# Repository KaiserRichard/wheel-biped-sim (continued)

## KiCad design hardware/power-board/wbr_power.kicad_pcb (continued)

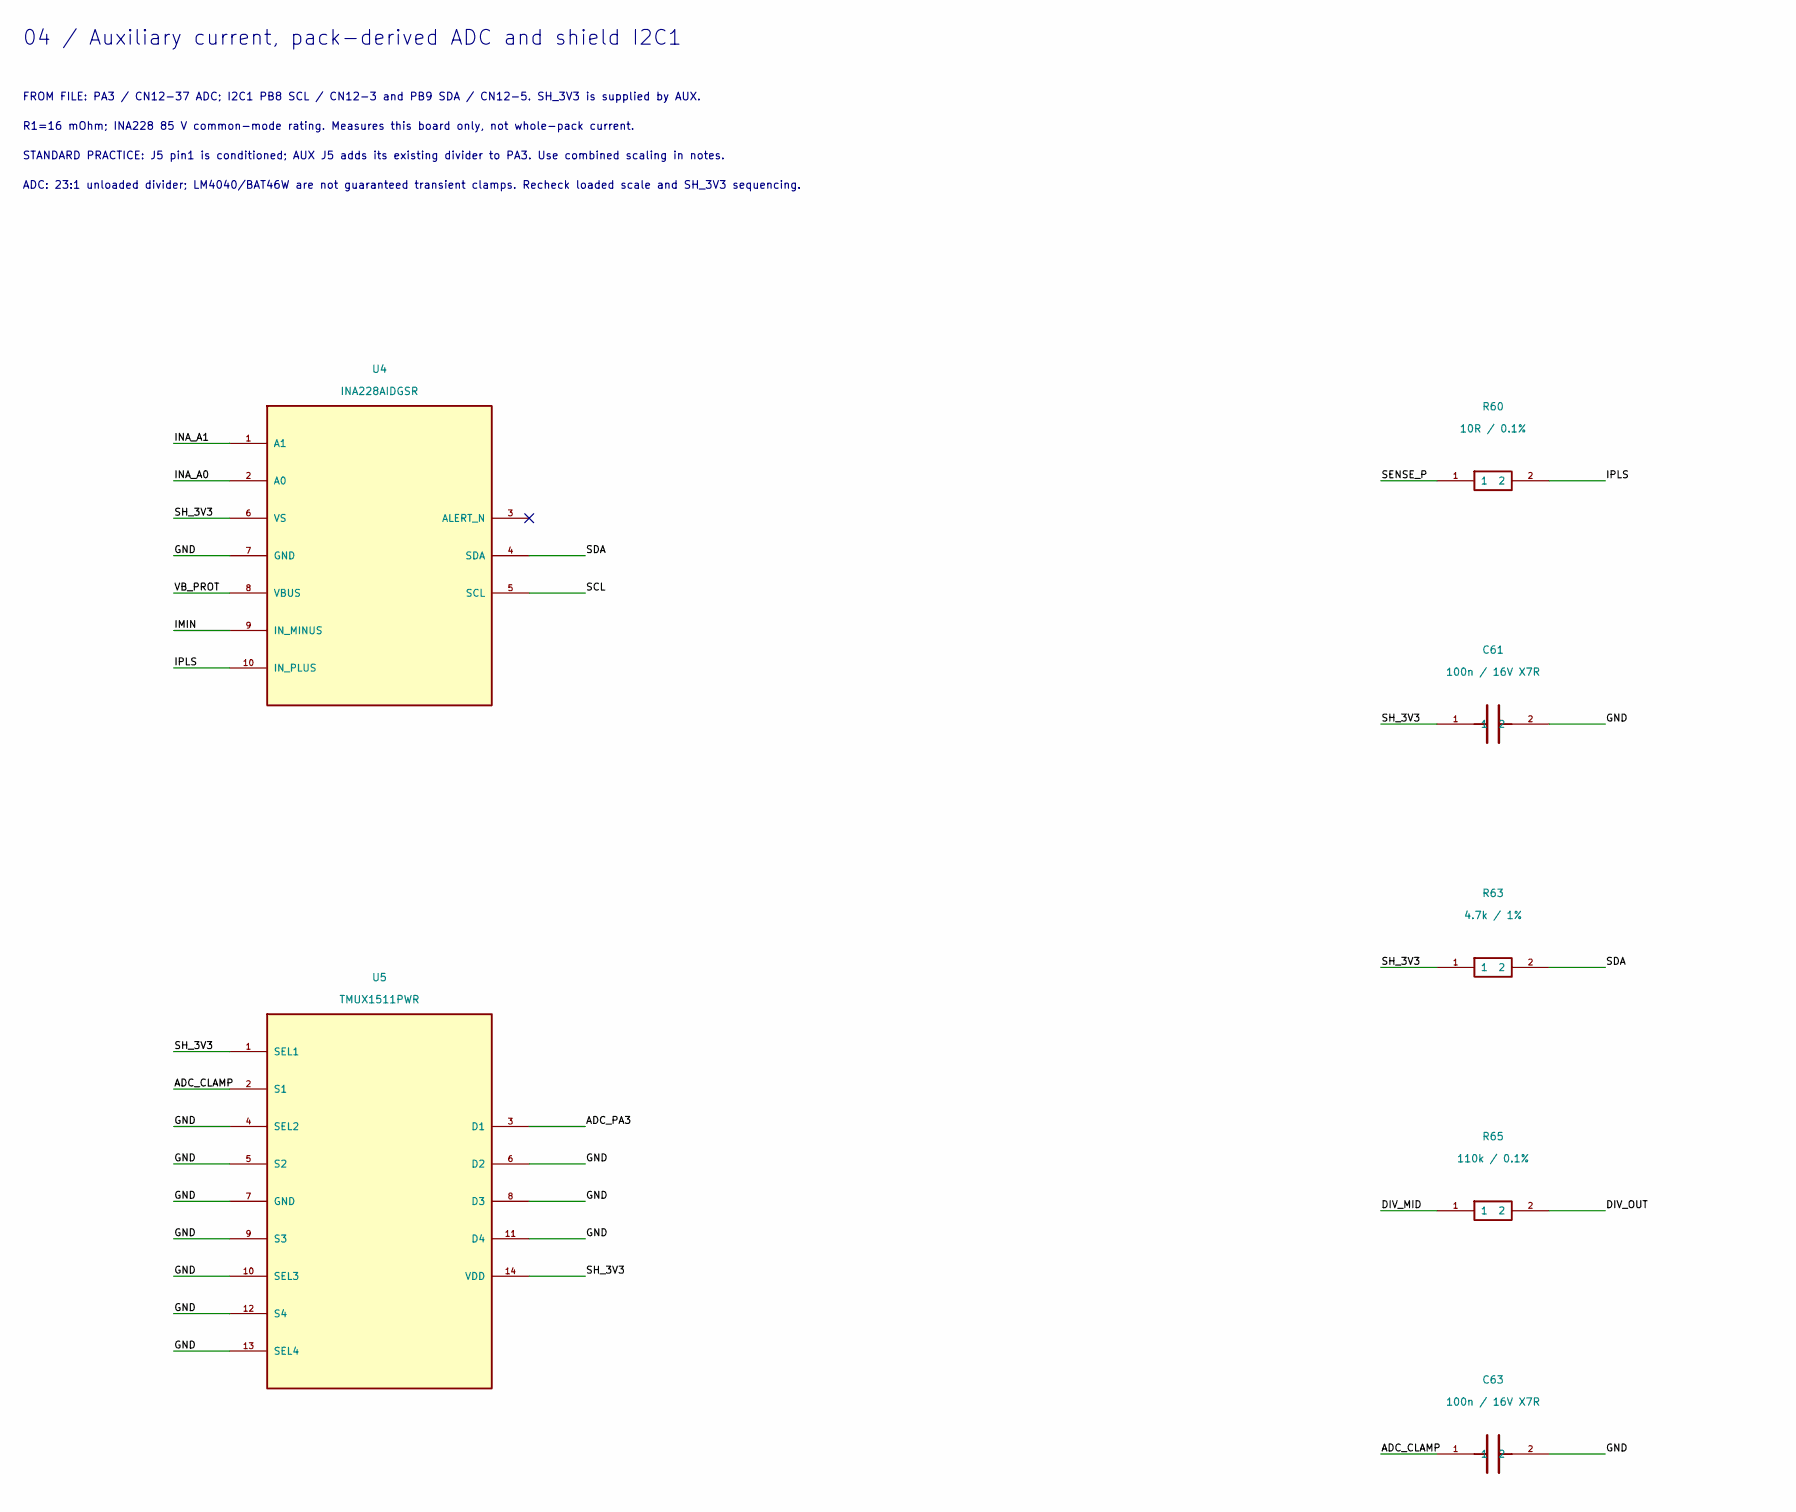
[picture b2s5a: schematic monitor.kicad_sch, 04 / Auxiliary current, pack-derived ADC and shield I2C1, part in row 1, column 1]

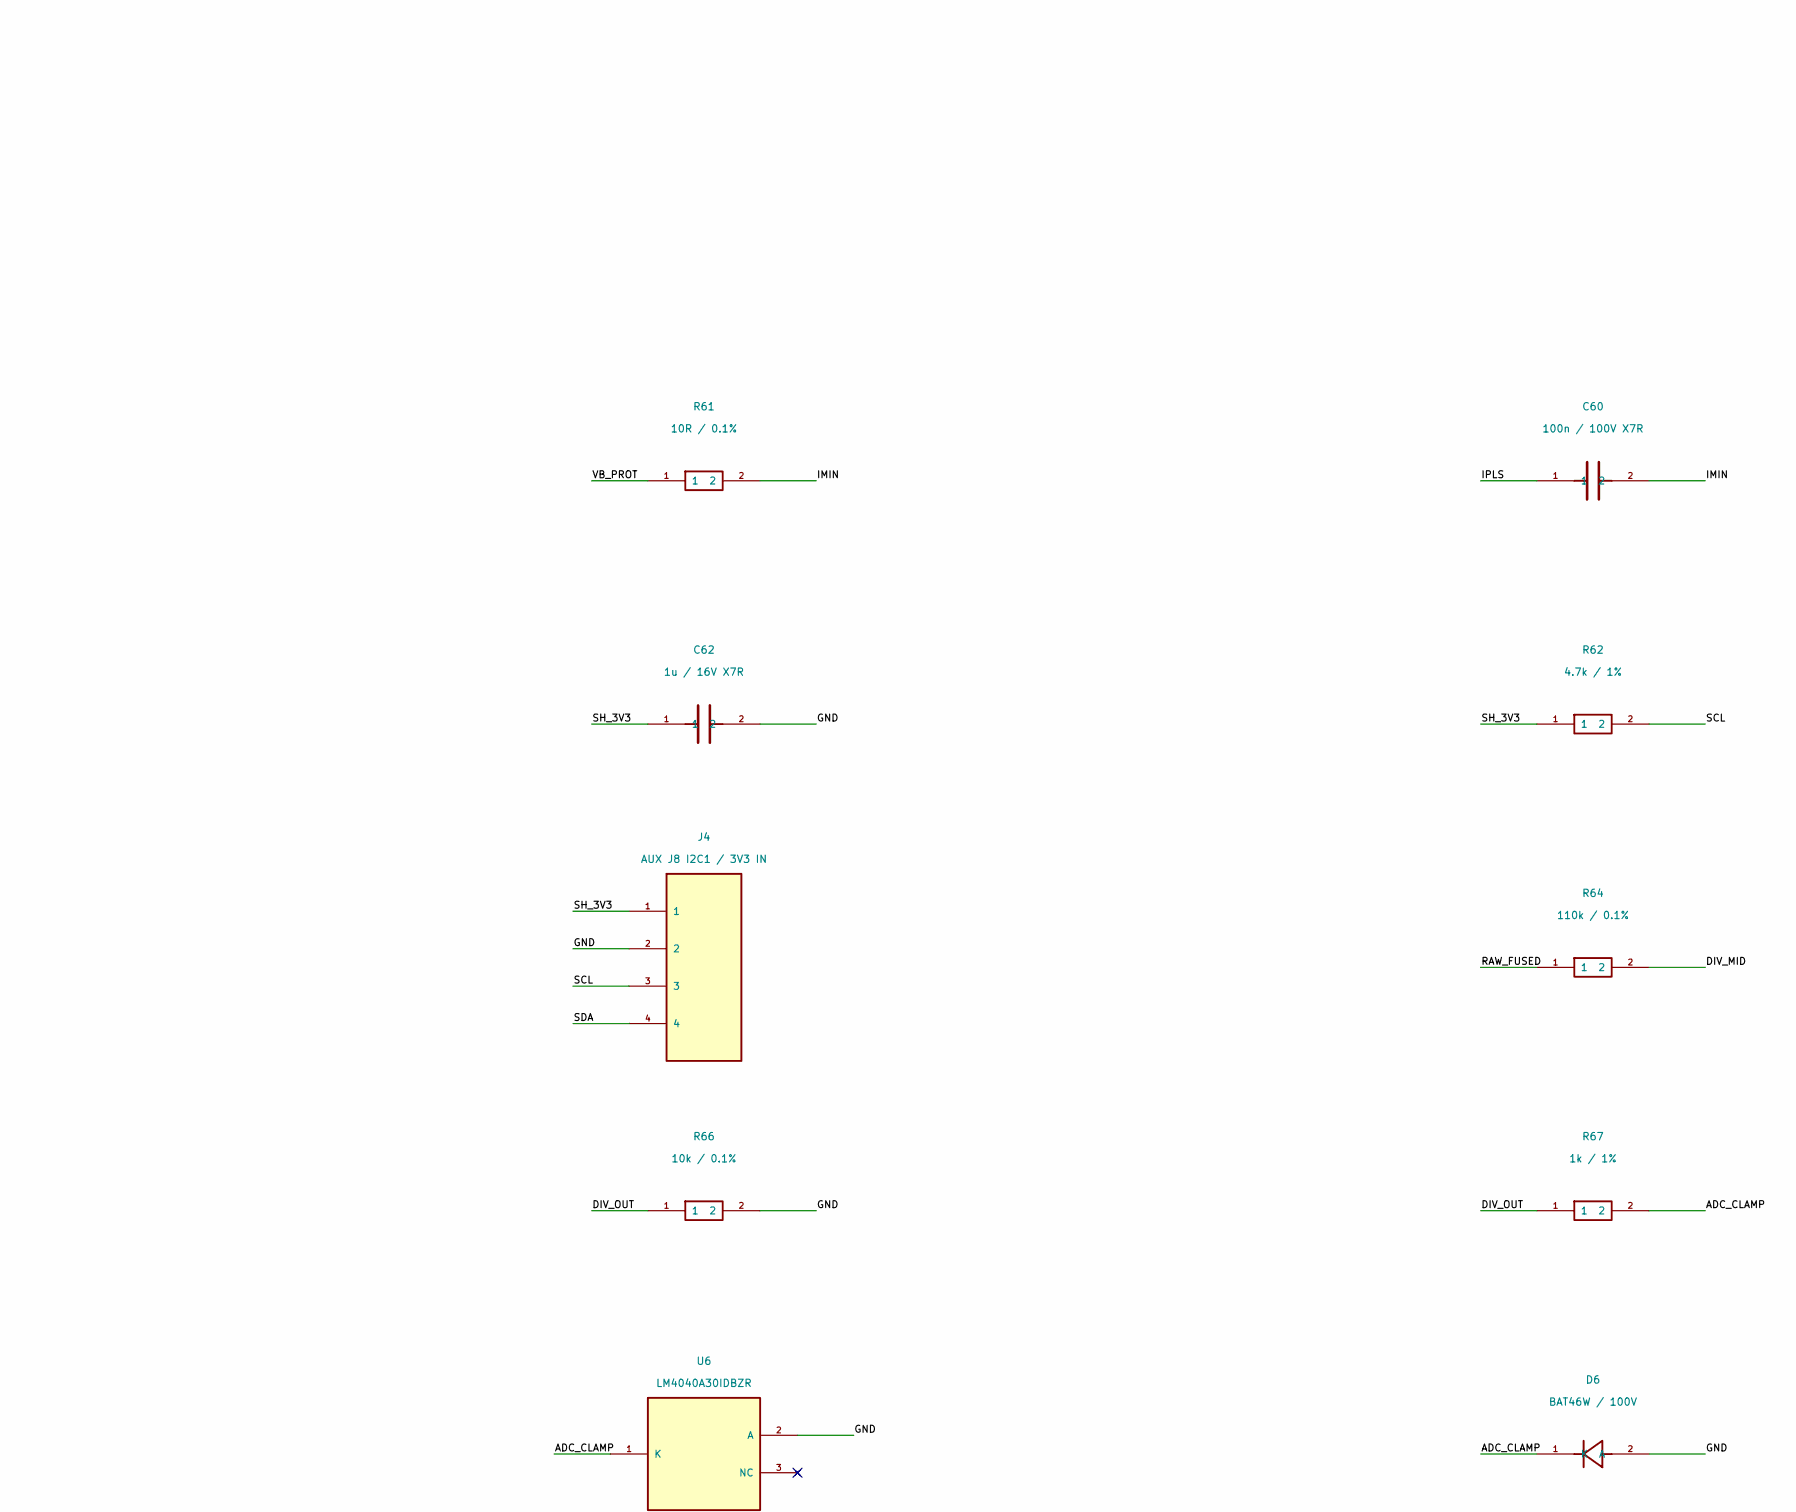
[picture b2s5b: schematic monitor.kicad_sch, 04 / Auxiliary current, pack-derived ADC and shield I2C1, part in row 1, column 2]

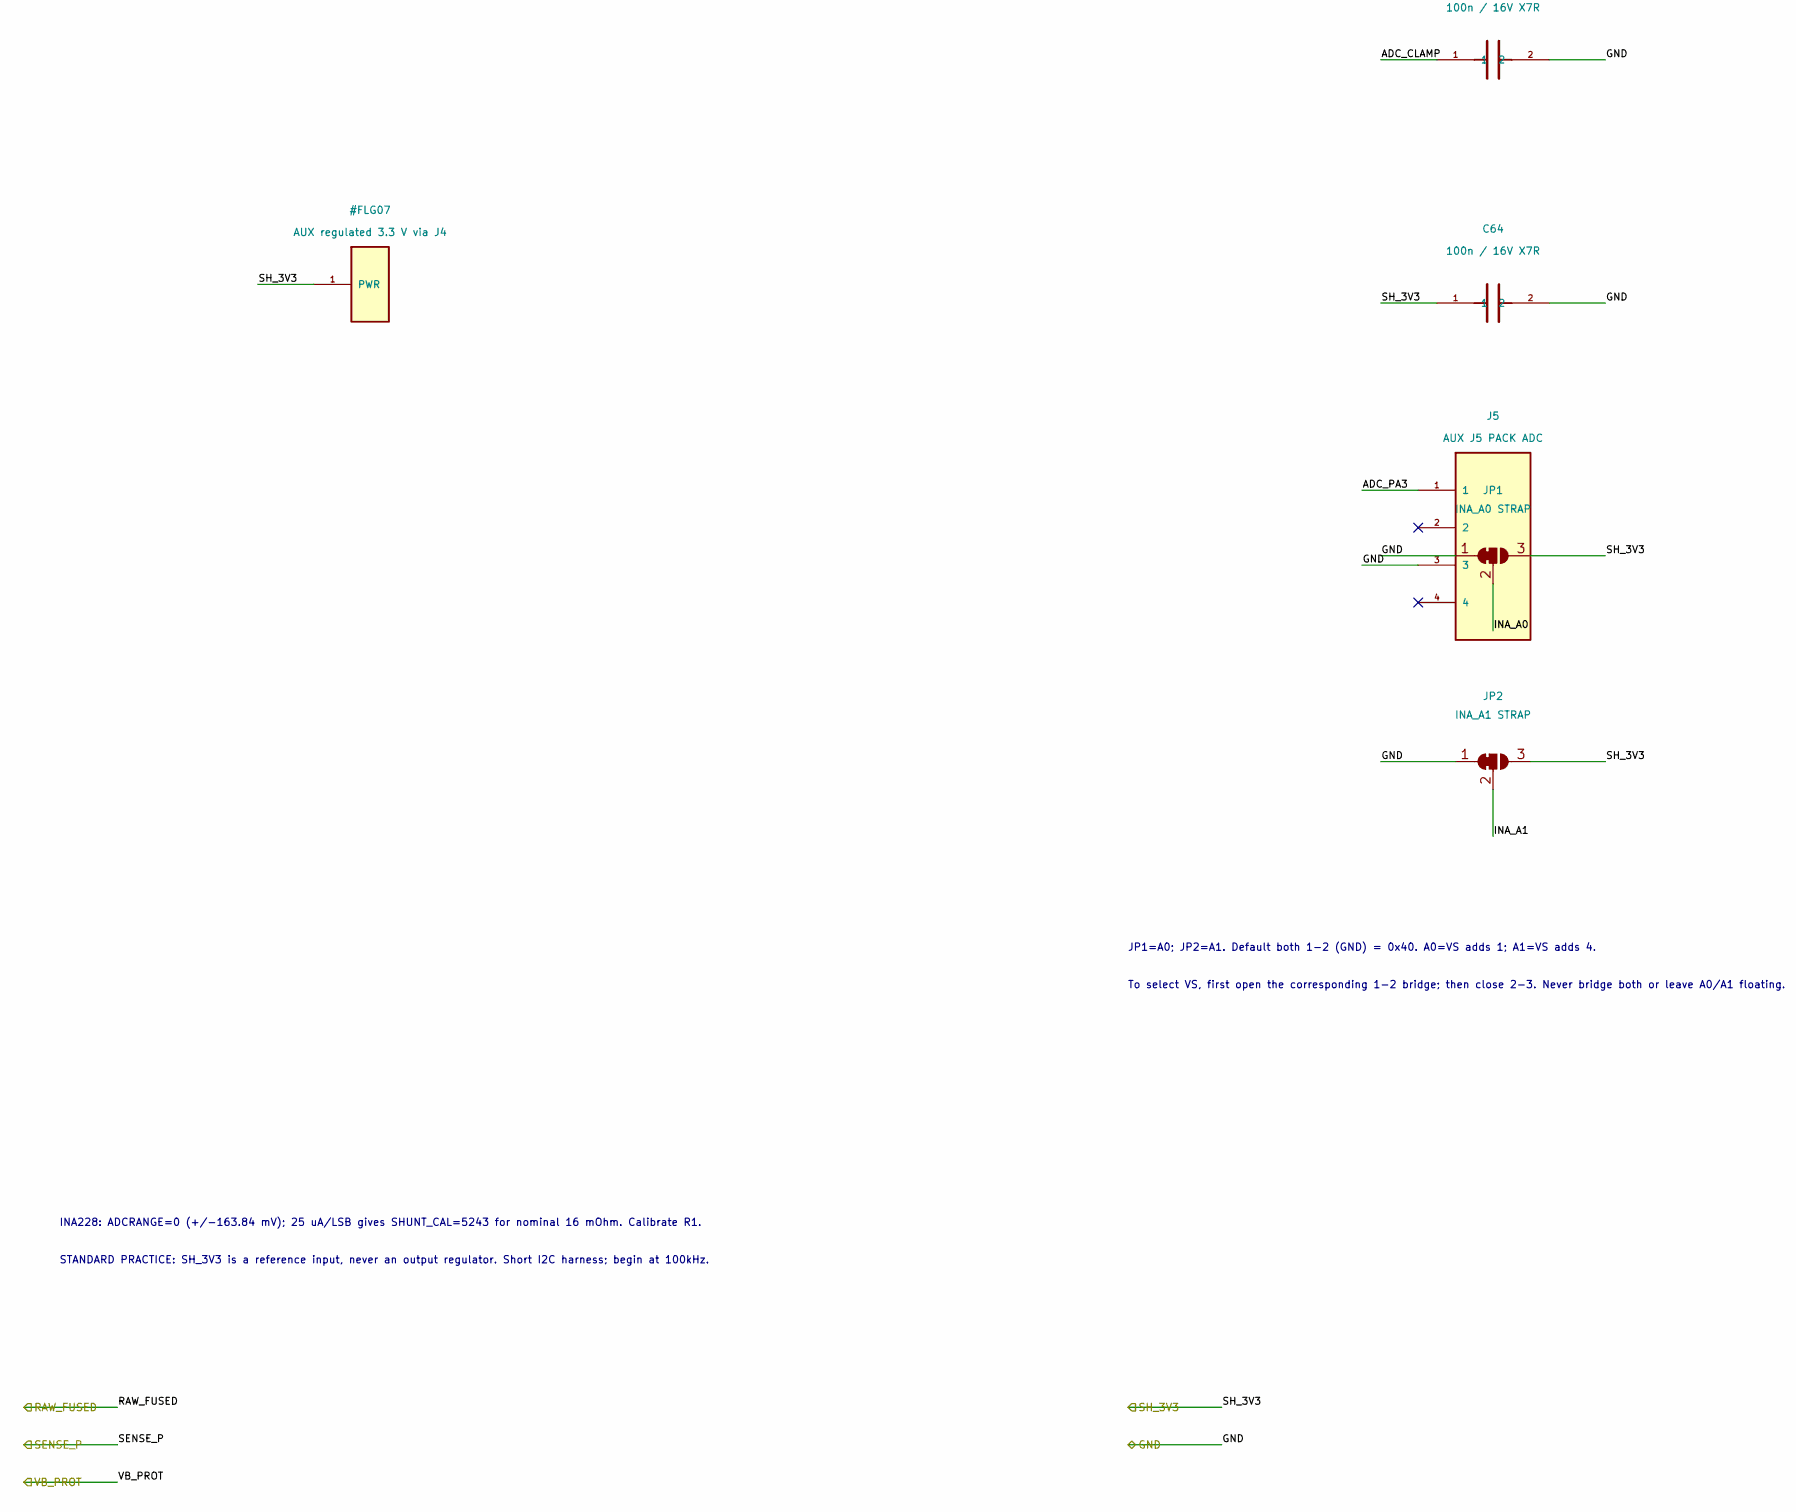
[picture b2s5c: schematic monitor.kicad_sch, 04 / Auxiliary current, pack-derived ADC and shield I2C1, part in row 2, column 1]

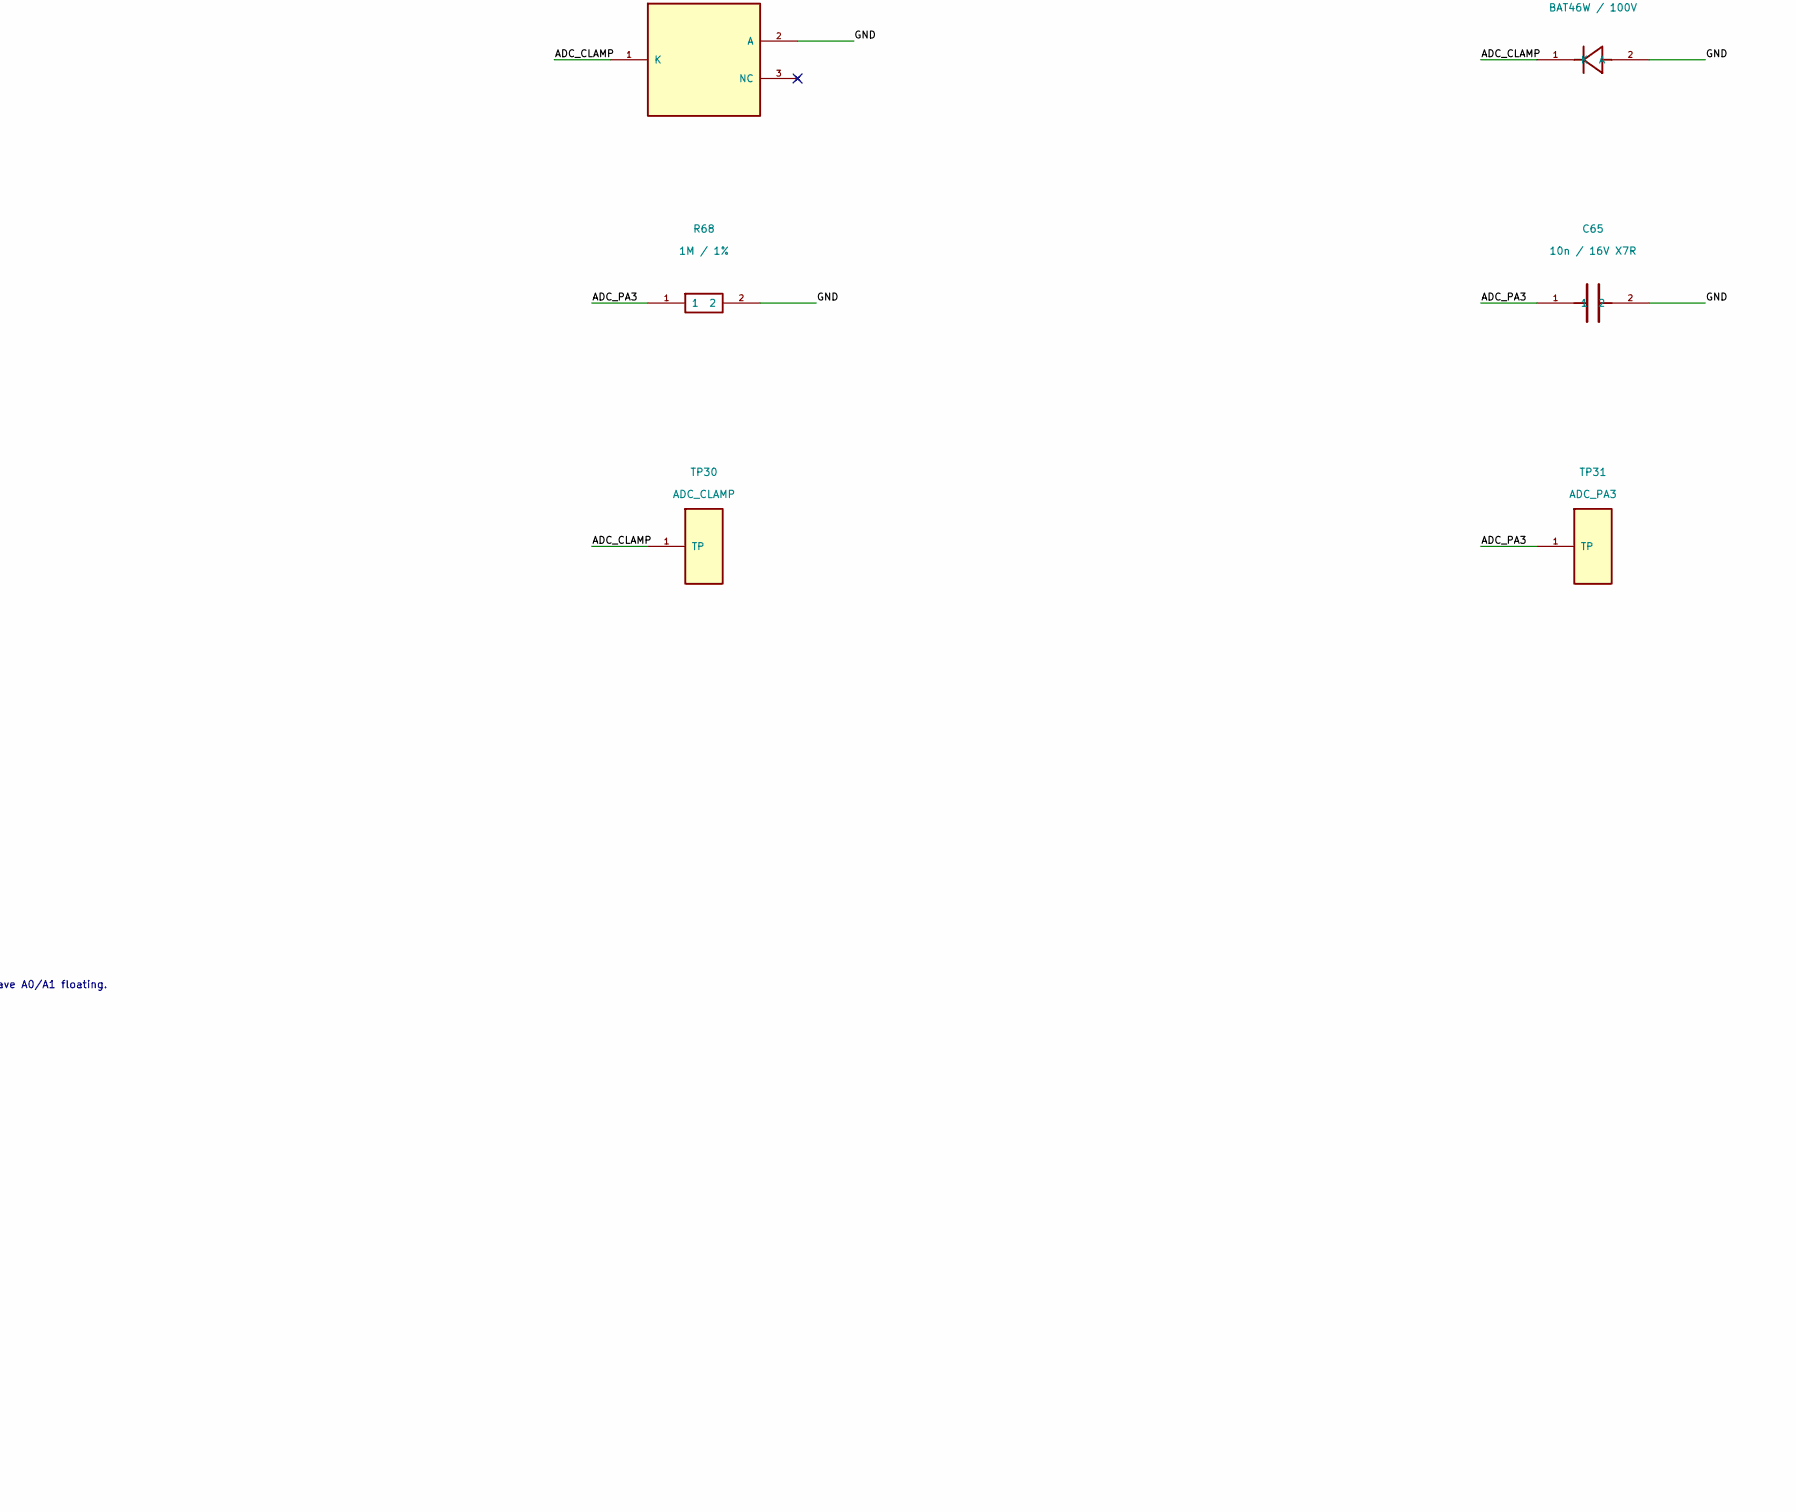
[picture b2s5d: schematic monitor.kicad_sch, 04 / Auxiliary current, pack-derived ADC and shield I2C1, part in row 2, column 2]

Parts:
C60: 100n / 100V X7R; C_1210_3225Metric; Rating 100 V; MPN 100n / 100V X7R
C61: 100n / 16V X7R; C_0805_2012Metric; Rating 16 V; U4 within 2mm; MPN 100n / 16V X7R
C62: 1u / 16V X7R; C_0805_2012Metric; Rating 16 V; U4 local bulk; MPN 1u / 16V X7R
C63: 100n / 16V X7R; C_0805_2012Metric; Rating 16 V; RC with divider Thevenin + R67; MPN 100n / 16V X7R
C64: 100n / 16V X7R; C_0805_2012Metric; Rating 16 V; U5 local decoupling; MPN 100n / 16V X7R
C65: 10n / 16V X7R; C_0805_2012Metric; Rating 16 V; ADC sampling charge reservoir; MPN 10n / 16V X7R
D6: BAT46W / 100V; D_SOD-123; Rating 100 V reverse; lower ADC clamp; MPN BAT46W / 100V
J4: AUX J8 I2C1 / 3V3 IN; JST_GH_BM04B-GHS-TBT_1x04-1MP_P1.25mm_Vertical; Rating 50 V connector; 3.3 V signals; pinout m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; MPN AUX J8 I2C1 / 3V3 IN
J5: AUX J5 PACK ADC; Molex_Micro-Fit_3.0_43045-0400_2x02_P3.00mm_Horizontal; Rating 250 V connector; conditioned pin1 / NC 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; MPN AUX J5 PACK ADC
JP1: INA_A0 STRAP; SolderJumper-3_P1.3mm_Bridged12_RoundedPad1.0x1.5mm
JP2: INA_A1 STRAP; SolderJumper-3_P1.3mm_Bridged12_RoundedPad1.0x1.5mm
R60, R61: 10R / 0.1%; R_1206_3216Metric; Rating 150 V; MPN 10R / 0.1%
R62, R63: 4.7k / 1%; R_0805_2012Metric; Rating 100 V; DNP if AUX already has pull-ups; MPN 4.7k / 1%
R64, R65: 110k / 0.1%; R_1206_3216Metric; Rating 150 V; MPN 110k / 0.1%
R66: 10k / 0.1%; R_1206_3216Metric; Rating 150 V; MPN 10k / 0.1%
R67: 1k / 1%; R_1206_3216Metric; Rating 150 V; MPN 1k / 1%
R68: 1M / 1%; R_0805_2012Metric; Rating 100 V; holds disconnected output low; MPN 1M / 1%
TP30: ADC_CLAMP; TestPoint_Pad_D2.0mm; Rating 0-3.01 V; MPN ADC_CLAMP
TP31: ADC_PA3; TestPoint_Pad_D2.0mm; Rating 0-3.01 V; MPN ADC_PA3
U4: INA228AIDGSR; VSSOP-10_3x3mm_P0.5mm; Rating 85 V IN+/IN-/VBUS; 2.7-5.5 V supply; MPN INA228AIDGSR
U5: TMUX1511PWR; TSSOP-14_4.4x5mm_P0.65mm; Rating supply 1.5-5.5 V; signal powered-off pr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; MPN TMUX1511PWR
U6: LM4040A30IDBZR; SOT-23; Rating 3.0 V shunt reference; >100uA clamp fau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; MPN LM4040A30IDBZR

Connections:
/GND: C61.2, C62.2, C63.2, C64.2, C65.2, D6.2 (A), J4.2, J5.3, JP1.1 (A), JP2.1 (A), R66.2, R68.2, U4.7 (GND), U5.4 (SEL2), U5.5 (S2), U5.6 (D2), U5.7 (GND), U5.8 (D3), U5.9 (S3), U5.10 (SEL3), U5.11 (D4), U5.12 (S4), U5.13 (SEL4), U6.2 (A); also elsewhere on the board
/RAW_FUSED: R64.1; also elsewhere on the board
/SENSE_P: R60.1; also elsewhere on the board
/SH_3V3: C61.1, C62.1, C64.1, J4.1, JP1.3 (B), JP2.3 (B), R62.1, R63.1, U4.6 (VS), U5.1 (SEL1), U5.14 (VDD); also elsewhere on the board
/VB_PROT: R61.1, U4.8 (VBUS); also elsewhere on the board
/monitor/ADC_CLAMP: C63.1, D6.1 (K), R67.2, TP30.1, U5.2 (S1), U6.1 (K)
/monitor/ADC_PA3: C65.1, J5.1, R68.1, TP31.1, U5.3 (D1)
/monitor/DIV_MID: R64.2, R65.1
/monitor/DIV_OUT: R65.2, R66.1, R67.1
/monitor/IMIN: C60.2, R61.2, U4.9 (IN_MINUS)
/monitor/INA_A0: JP1.2 (C), U4.2 (A0)
/monitor/INA_A1: JP2.2 (C), U4.1 (A1)
/monitor/IPLS: C60.1, R60.2, U4.10 (IN_PLUS)
/monitor/SCL: J4.3, R62.2, U4.5 (SCL)
/monitor/SDA: J4.4, R63.2, U4.4 (SDA)

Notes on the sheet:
04 / Auxiliary current, pack-derived ADC and shield I2C1
FROM FILE: PA3 / CN12-37 ADC; I2C1 PB8 SCL / CN12-3 and PB9 SDA / CN12-5. SH_3V3 is supplied by AUX.
R1=16 mOhm; INA228 85 V common-mode rating. Measures this board only, not whole-pack current.
STANDARD PRACTICE: J5 pin1 is conditioned; AUX J5 adds its existing divider to PA3. Use combined scaling in notes.
ADC: 23:1 unloaded divider; LM4040/BAT46W are not guaranteed transient clamps. Recheck loaded scale and SH_3V3 sequencing.
INA228: ADCRANGE=0 (+/-163.84 mV); 25 uA/LSB gives SHUNT_CAL=5243 for nominal 16 mOhm. Calibrate R1.
STANDARD PRACTICE: SH_3V3 is a reference input, never an output regulator. Short I2C harness; begin at 100kHz.
JP1=A0; JP2=A1. Default both 1-2 (GND) = 0x40. A0=VS adds 1; A1=VS adds 4.
To select VS, first open the corresponding 1-2 bridge; then close 2-3. Never bridge both or leave A0/A1 floating.

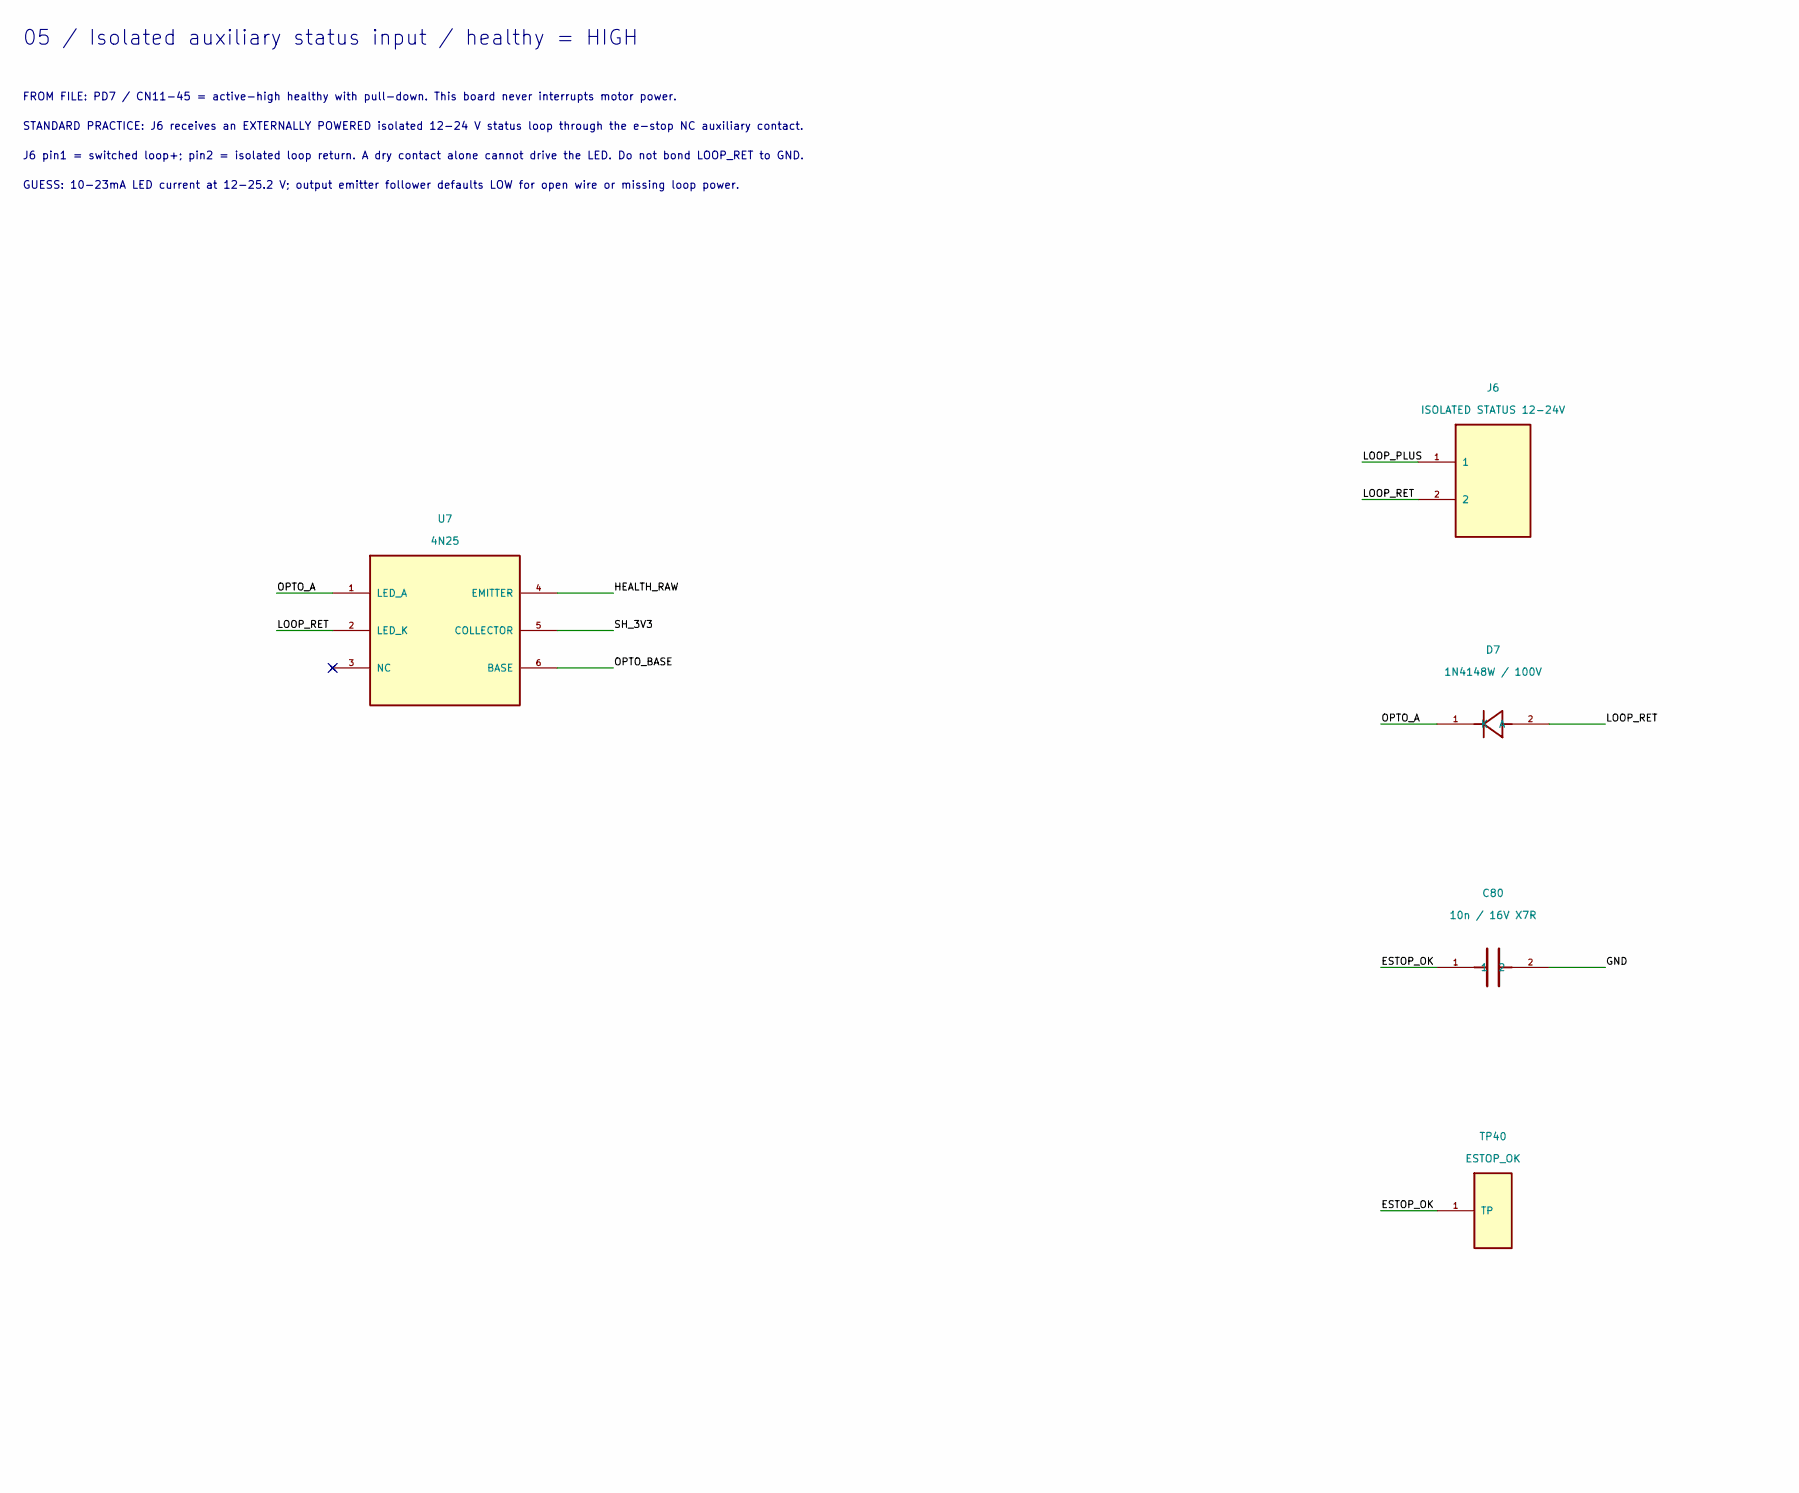
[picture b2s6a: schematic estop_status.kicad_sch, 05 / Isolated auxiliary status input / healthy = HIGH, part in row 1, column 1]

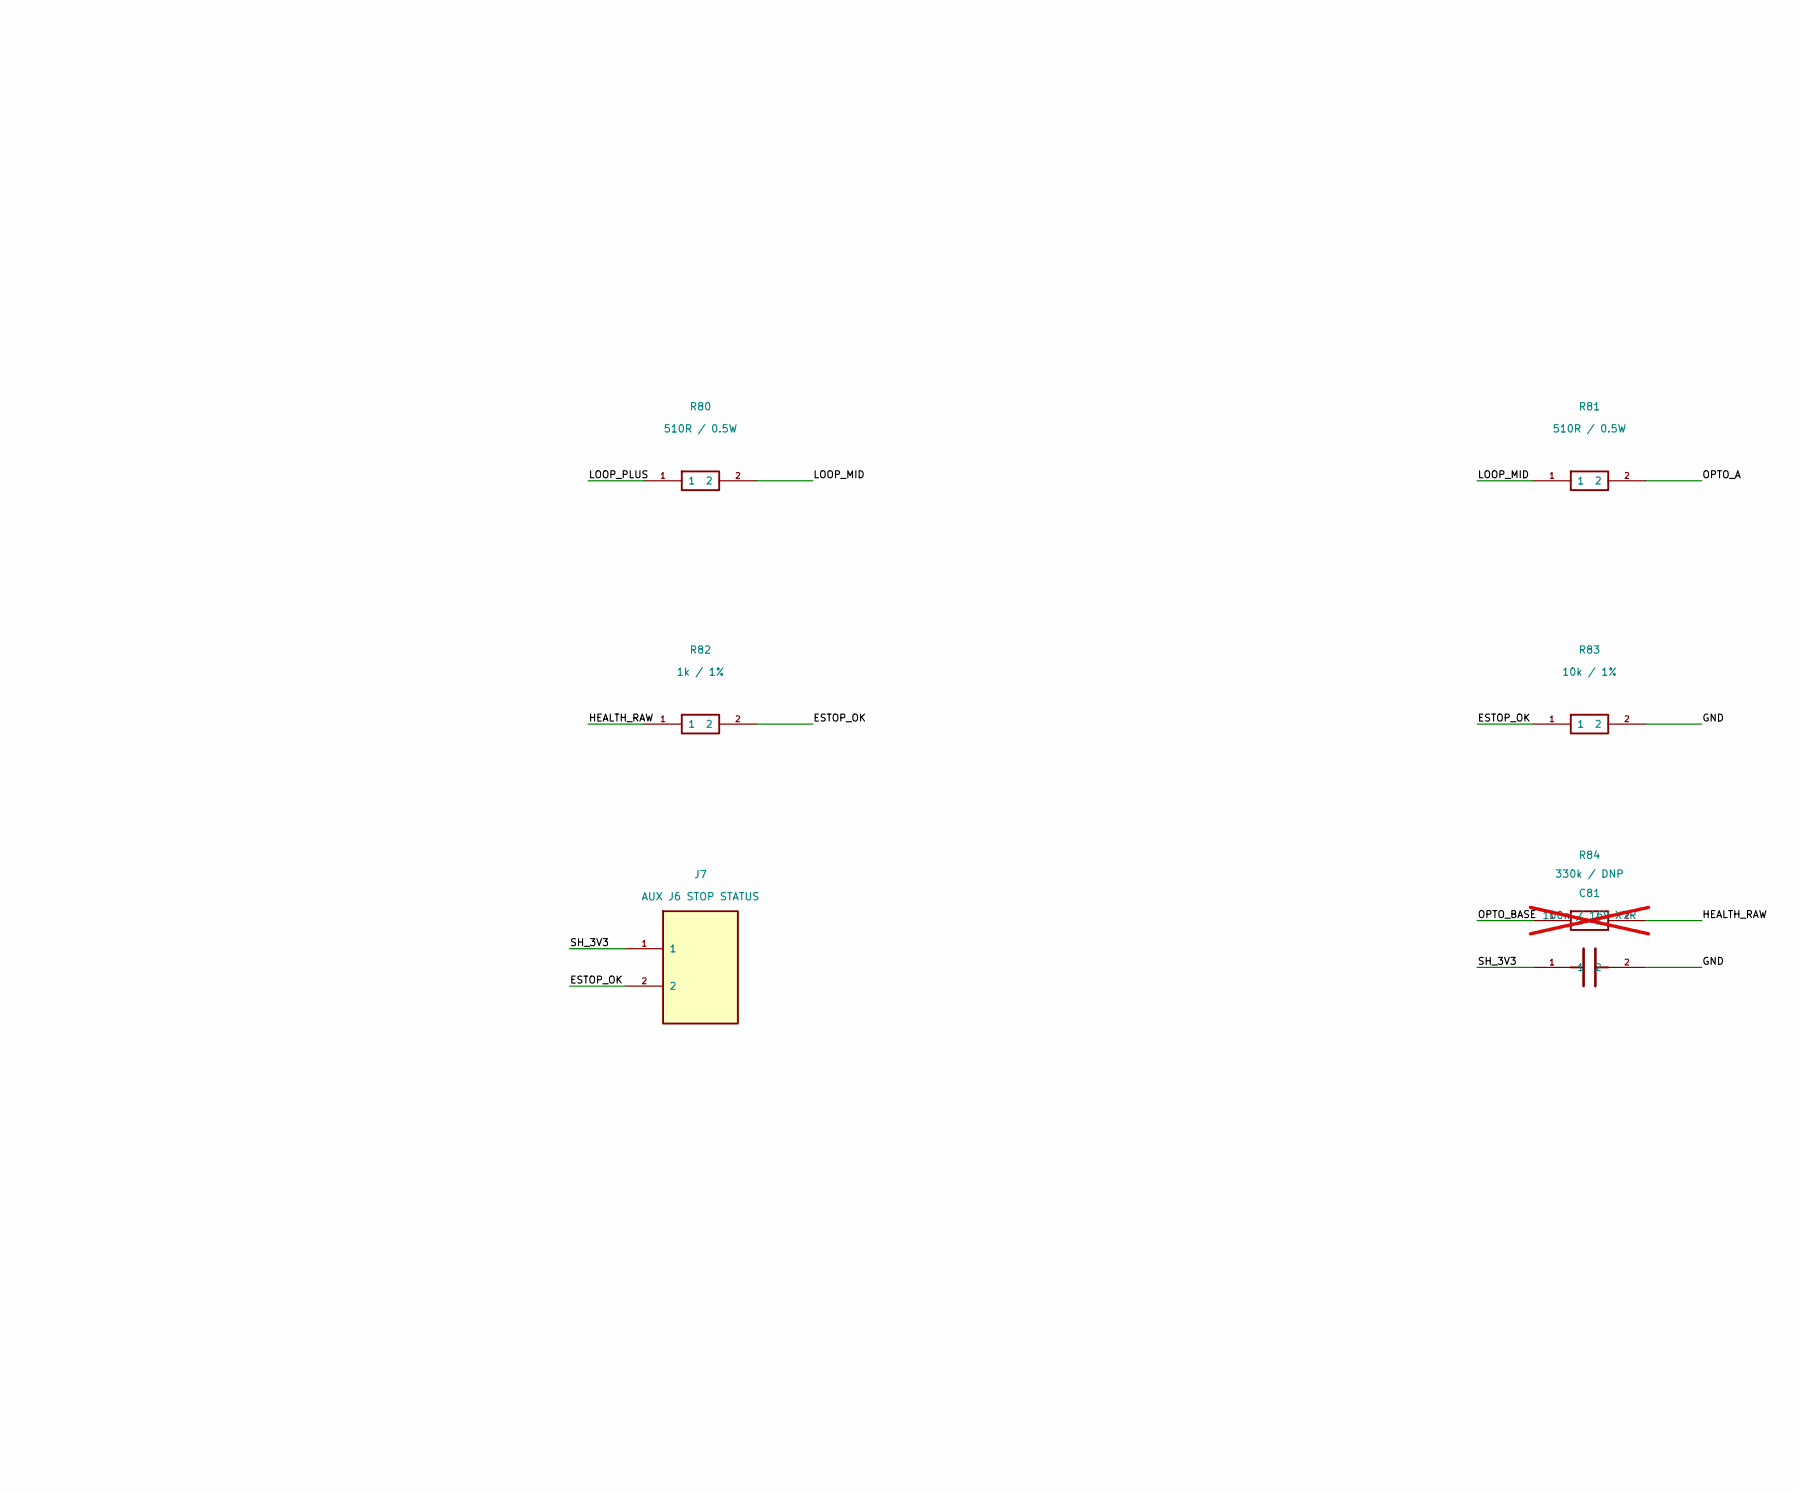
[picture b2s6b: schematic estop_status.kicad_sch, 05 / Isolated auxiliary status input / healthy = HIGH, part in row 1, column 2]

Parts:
C80: 10n / 16V X7R; C_0805_2012Metric; Rating 16 V; RC status filter; MPN 10n / 16V X7R
C81: 100n / 16V X7R; C_0805_2012Metric; Rating 16 V; connector local bypass; MPN 100n / 16V X7R
D7: 1N4148W / 100V; D_SOD-123; Rating 100 V; antiparallel LED reverse protect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; MPN 1N4148W / 100V
J6: ISOLATED STATUS 12-24V; TerminalBlock_Phoenix_MKDS-3-2-5.08_1x02_P5.08mm_Horizontal; Rating 250 V connector; SELV loop only; MPN ISOLATED STATUS 12-24V
J7: AUX J6 STOP STATUS; Molex_Micro-Fit_3.0_43045-0200_2x01_P3.00mm_Horizontal; Rating 250 V connector; pin1 3V3 IN / pin2 HEA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; MPN AUX J6 STOP STATUS
R80, R81: 510R / 0.5W; R_1206_3216Metric; Rating 150 V; 0.5 W; MPN 510R / 0.5W
R82: 1k / 1%; R_0805_2012Metric; Rating 100 V; MPN 1k / 1%
R83: 10k / 1%; R_0805_2012Metric; Rating 100 V; mandatory default not healthy; MPN 10k / 1%
R84: 330k / DNP; R_0805_2012Metric; not fitted
TP40: ESTOP_OK; TestPoint_Pad_D2.0mm; Rating 3.3 V class; MPN ESTOP_OK
U7: 4N25; DIP-6_W7.62mm; Rating 5kVrms optical isolation test; not a sa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; MPN 4N25

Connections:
/GND: C80.2, C81.2, R83.2; also elsewhere on the board
/SH_3V3: C81.1, J7.1, U7.5 (COLLECTOR); also elsewhere on the board
/estop_status/ESTOP_OK: C80.1, J7.2, R82.2, R83.1, TP40.1
/estop_status/HEALTH_RAW: R82.1, R84.2, U7.4 (EMITTER)
/estop_status/LOOP_MID: R80.2, R81.1
/estop_status/LOOP_PLUS: J6.1, R80.1
/estop_status/LOOP_RET: D7.2 (A), J6.2, U7.2 (LED_K)
/estop_status/OPTO_A: D7.1 (K), R81.2, U7.1 (LED_A)
/estop_status/OPTO_BASE: R84.1, U7.6 (BASE)

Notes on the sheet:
05 / Isolated auxiliary status input / healthy = HIGH
FROM FILE: PD7 / CN11-45 = active-high healthy with pull-down. This board never interrupts motor power.
STANDARD PRACTICE: J6 receives an EXTERNALLY POWERED isolated 12-24 V status loop through the e-stop NC auxiliary contact.
J6 pin1 = switched loop+; pin2 = isolated loop return. A dry contact alone cannot drive the LED. Do not bond LOOP_RET to GND.
GUESS: 10-23mA LED current at 12-25.2 V; output emitter follower defaults LOW for open wire or missing loop power.
STANDARD PRACTICE: contact closed + powered loop => HIGH healthy; contact open, broken wire or loss of power => LOW.
A short across the contact can look healthy. This status input is not a certified or redundant safety channel.
The independent motor-power e-stop, manual reset and inspection remain external robot work / TBD.
R84 is optional (DNP). Evaluate turn-off and worst-case healthy voltage before fitting.
